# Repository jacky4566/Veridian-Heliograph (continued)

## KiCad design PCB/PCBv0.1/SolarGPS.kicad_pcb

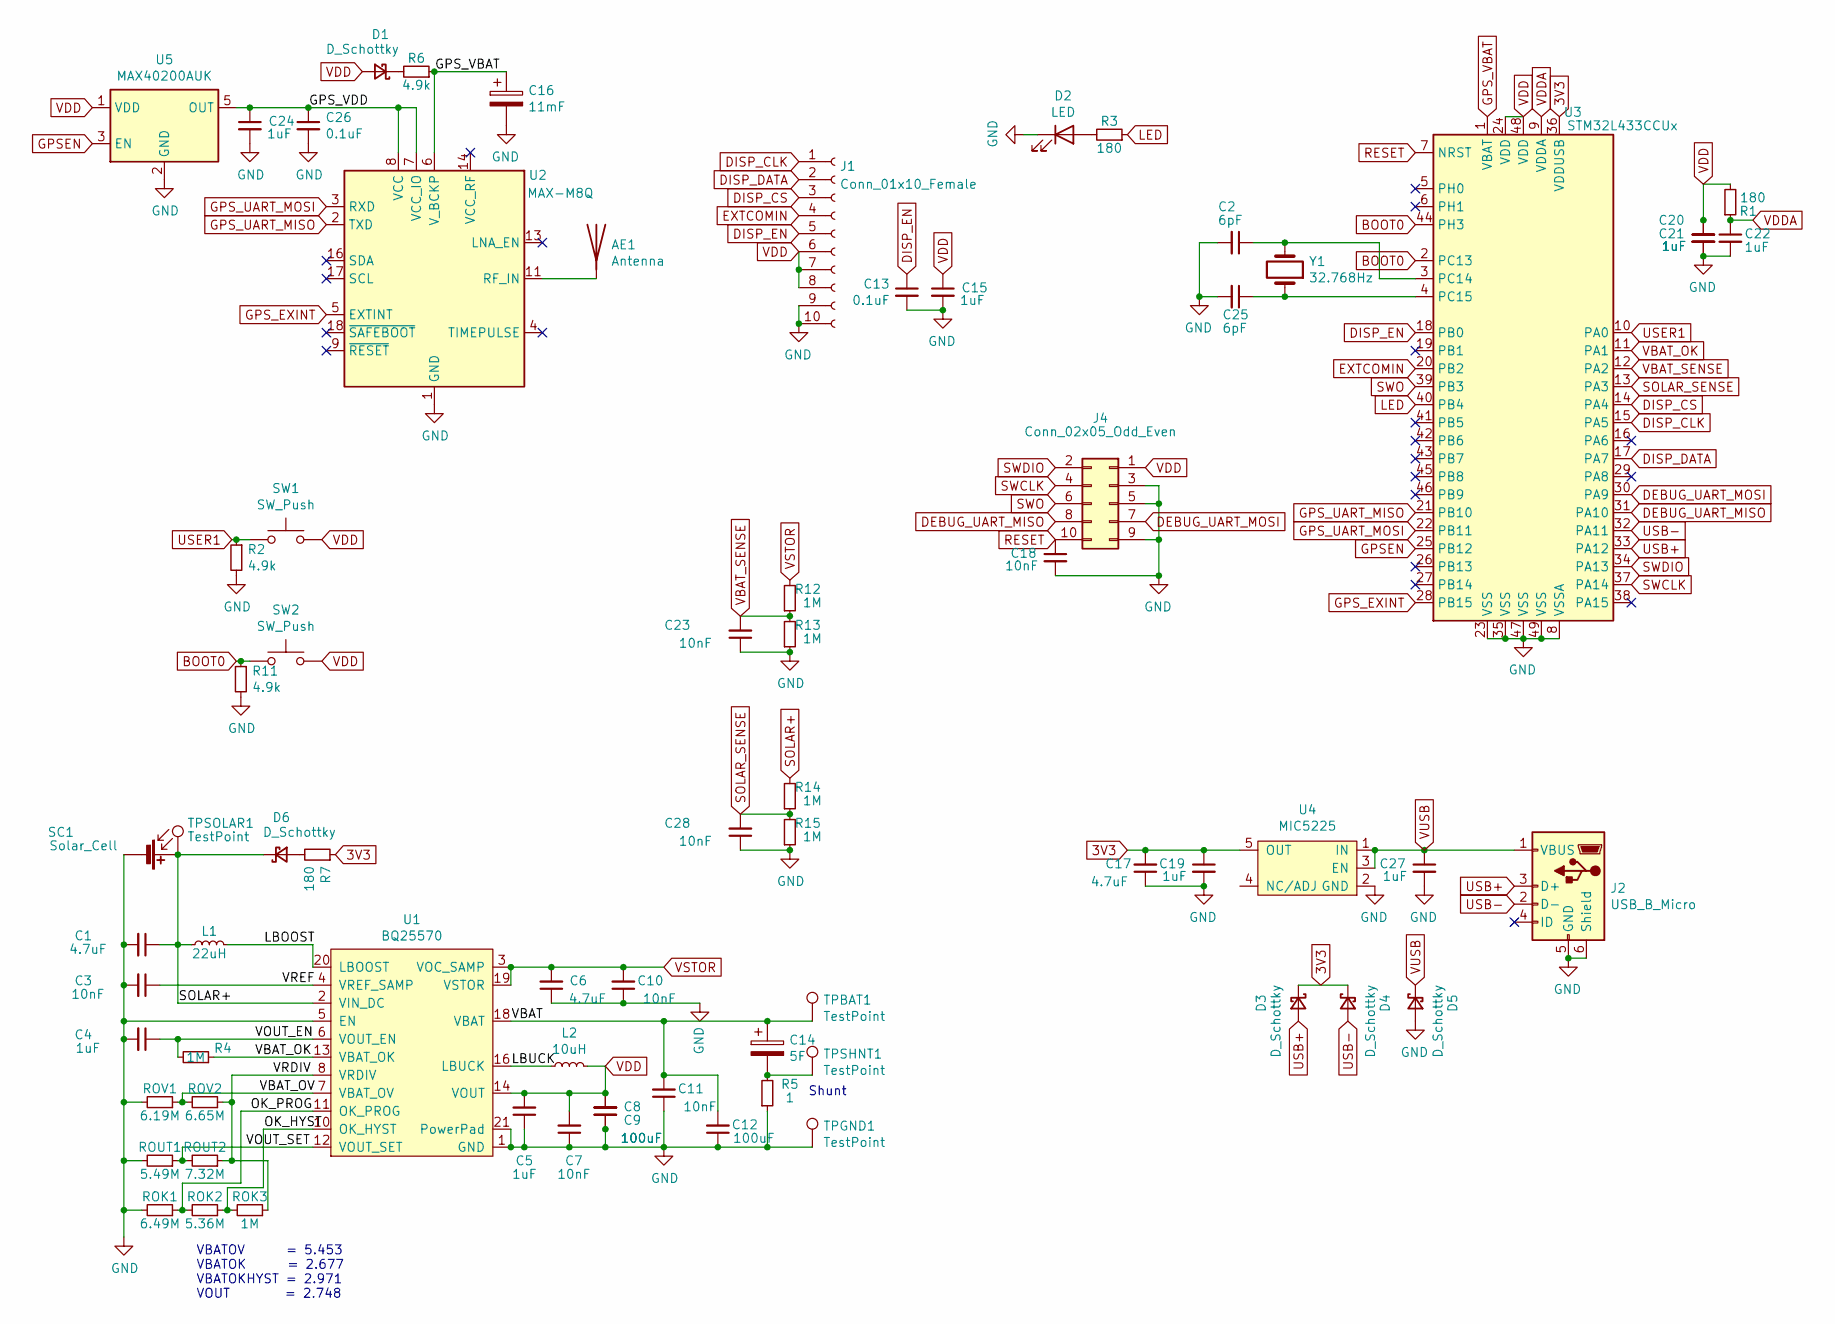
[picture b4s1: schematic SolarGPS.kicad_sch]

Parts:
AE1: Antenna; CGIP.25.4.A.02
C1, C6, C17: 4.7uF; C_0805_2012Metric
C2, C25: 6pF; C_0603_1608Metric
C3, C7, C10, C11, C18, C23, C28: 10nF; C_0603_1608Metric
C4, C5, C15, C19, C20, C21, C22, C24, C27: 1uF; C_0603_1608Metric
C8, C9, C12: 100uF; C_1206_3216Metric
C13, C26: 0.1uF; C_0603_1608Metric
C14: 5F; PinHeader_1x02_P2.54mm_Vertical
C16: 11mF; C_1210_3225Metric; Part CPH3225A
D1, D3, D4, D5, D6: D_Schottky; D_SOD-523
D2: LED; D_0805_2012Metric; PArt LTST-S270CKT
J1: Conn_01x10_Female; AYF531035
J2: USB_B_Micro; USB_Micro-B_GCT_USB3076-30-A
J4: Conn_02x05_Odd_Even; PinHeader_2x05_P2.00mm_Vertical_SMD
L1: 22uH; 744031220; Part 744031220
L2: 10uH; 744029100; Part 744029100
R1, R3, R7: 180; R_0603_1608Metric
R2, R6, R11: 4.9k; R_0603_1608Metric
R4, R12, R13, R14, R15: 1M; R_0603_1608Metric
R5: 1; R_0603_1608Metric
ROK1: 6.49M; R_0603_1608Metric
ROK2: 5.36M; R_0603_1608Metric
ROK3: 1M; R_0603_1608Metric
ROUT1: 5.49M; R_0603_1608Metric
ROUT2: 7.32M; R_0603_1608Metric
ROV1: 6.19M; R_0603_1608Metric
ROV2: 6.65M; R_0603_1608Metric
SC1: Solar_Cell; SM141K09L
SW1, SW2: SW_Push; SW_Push_1P1T_NO_6x6mm_H9.5mm; Part KSC471G 70SH LFS PF
TPBAT1: TestPoint; TestPoint_THTPad_1.0x1.0mm_Drill0.5mm
TPGND1: TestPoint; TestPoint_THTPad_1.0x1.0mm_Drill0.5mm
TPSHNT1: TestPoint; TestPoint_THTPad_1.0x1.0mm_Drill0.5mm
TPSOLAR1: TestPoint; TestPoint_THTPad_1.0x1.0mm_Drill0.5mm
U1: BQ25570; QFN-20-1EP_3.5x3.5mm_P0.5mm_EP2x2mm
U2: MAX-M8Q; ublox_MAX
U3: STM32L433CCUx; QFN-48-1EP_7x7mm_P0.5mm_EP5.6x5.6mm
U4: MIC5225; SOT-23-5
U5: MAX40200AUK; SOT-23-5
Y1: 32.768Hz; Crystal_SMD_3215-2Pin_3.2x1.5mm; Part CM315D

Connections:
3V3: C17.2, C19.1, D3.1 (K), D4.1 (K), R7.1, U3.36 (VDDUSB), U4.5 (OUT)
/GPS_VDD: C24.1, C26.1, U2.7 (VCC_IO), U2.8 (VCC), U5.5 (OUT)
/LBOOST: L1.2, U1.20 (LBOOST)
/LBUCK: L2.1, U1.16 (LBUCK)
/OK_HYST: ROK2.1, ROK3.2, U1.10 (OK_HYST)
/OK_PROG: ROK1.1, ROK2.2, U1.11 (OK_PROG)
/VBAT: C11.2, C12.2, C14.1, TPBAT1.1, U1.18 (VBAT)
/VBAT_OV: ROV1.1, ROV2.2, U1.7 (VBAT_OV)
/VOUT_EN: C4.1, R4.2, U1.6 (VOUT_EN)
/VOUT_SET: ROUT1.1, ROUT2.2, U1.12 (VOUT_SET)
/VRDIV: ROK3.1, ROUT2.1, ROV2.1, U1.8 (VRDIV)
/VREF: C3.1, U1.4 (VREF_SAMP)
BOOT0: R11.1, SW2.1, U3.2 (PC13), U3.44 (PH3)
DEBUG_UART_MISO: J4.8, U3.31 (PA10)
DEBUG_UART_MOSI: J4.7, U3.30 (PA9)
DISP_CLK: J1.1, U3.15 (PA5)
DISP_CS: J1.3, U3.14 (PA4)
DISP_DATA: J1.2, U3.17 (PA7)
DISP_EN: C13.1, J1.5, U3.18 (PB0)
EXTCOMIN: J1.4, U3.20 (PB2)
GND: C1.2, C2.2, C3.2, C4.2, C5.1, C6.1, C7.1, C8.1, C9.1, C10.1, C11.1, C12.1, C13.2, C15.2, C16.2, C17.1, C18.2, C19.2, C20.2, C21.2, C22.2, C23.1, C24.2, C25.2, C26.2, C27.2, C28.1, D2.1 (K), D5.2 (A), J1.9, J1.10, J2.5 (GND), J2.6 (Shield), J4.3, J4.5, J4.9, R2.2, R5.1, R11.2, R13.1, R15.1, ROK1.2, ROUT1.2, ROV1.2, SC1.2 (-), TPGND1.1, U1.1 (GND), U1.5 (EN), U1.9 (GND), U1.15 (GND), U1.17 (GND), U1.21 (PowerPad), U2.1 (GND), U2.10 (GND), U2.12 (GND), U3.8 (VSSA), U3.23 (VSS), U3.35 (VSS), U3.47 (VSS), U3.49 (VSS), U4.2 (GND), U5.2 (GND)
GPSEN: U3.25 (PB12), U5.3 (EN)
GPS_EXINT: U2.5 (EXTINT), U3.28 (PB15)
GPS_UART_MISO: U2.2 (TXD), U3.21 (PB10)
GPS_UART_MOSI: U2.3 (RXD), U3.22 (PB11)
GPS_VBAT: C16.1, R6.1, U2.6 (V_BCKP), U3.1 (VBAT)
LED: R3.1, U3.40 (PB4)
unnamed: AE1.1 (A), U2.11 (RF_IN)
unnamed: C2.1, U3.3 (PC14), Y1.2
unnamed: C14.2, R5.2, TPSHNT1.1
unnamed: C25.1, U3.4 (PC15), Y1.1
unnamed: D1.1 (K), R6.2
unnamed: D2.2 (A), R3.2
unnamed: D6.2 (A), R7.2
RESET: C18.1, J4.10, U3.7 (NRST)
SOLAR+: C1.1, D6.1 (K), L1.1, R14.2, SC1.1 (+), TPSOLAR1.1, U1.2 (VIN_DC)
SOLAR_SENSE: C28.2, R14.1, R15.2, U3.13 (PA3)
SWCLK: J4.4, U3.37 (PA14)
SWDIO: J4.2, U3.34 (PA13)
SWO: J4.6, U3.39 (PB3)
USB+: D3.2 (A), J2.3 (D+), U3.33 (PA12)
USB-: D4.2 (A), J2.2 (D-), U3.32 (PA11)
USER1: R2.1, SW1.1, U3.10 (PA0)
VBAT_OK: R4.1, U1.13 (VBAT_OK), U3.11 (PA1)
VBAT_SENSE: C23.2, R12.1, R13.2, U3.12 (PA2)
VDD: C5.2, C7.2, C8.2, C9.2, C15.1, C20.1, C21.1, D1.2 (A), J1.6, J1.7, J1.8, J4.1, L2.2, R1.2, SW1.2, SW2.2, U1.14 (VOUT), U3.24 (VDD), U3.48 (VDD), U5.1 (VDD)
VDDA: C22.1, R1.1, U3.9 (VDDA)
VSTOR: C6.2, C10.2, R12.2, U1.3 (VOC_SAMP), U1.19 (VSTOR)
VUSB: C27.1, D5.1 (K), J2.1 (VBUS), U4.1 (IN), U4.3 (EN)

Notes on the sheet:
VBATOV = 5.453 VBATOK = 2.677 VBATOKHYST = 2.971 VOUT = 2.748
Shunt

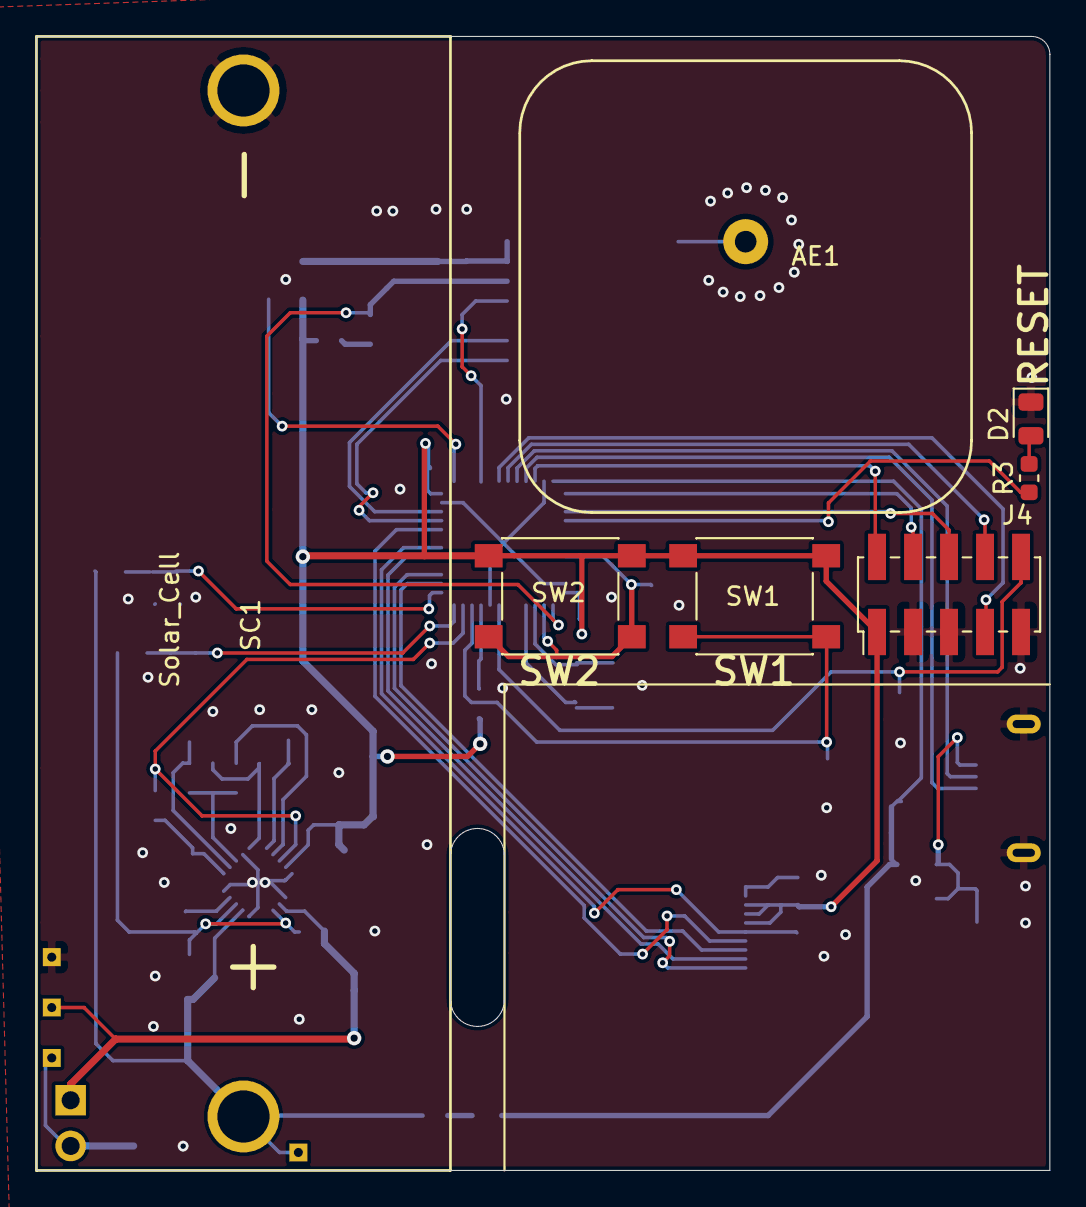
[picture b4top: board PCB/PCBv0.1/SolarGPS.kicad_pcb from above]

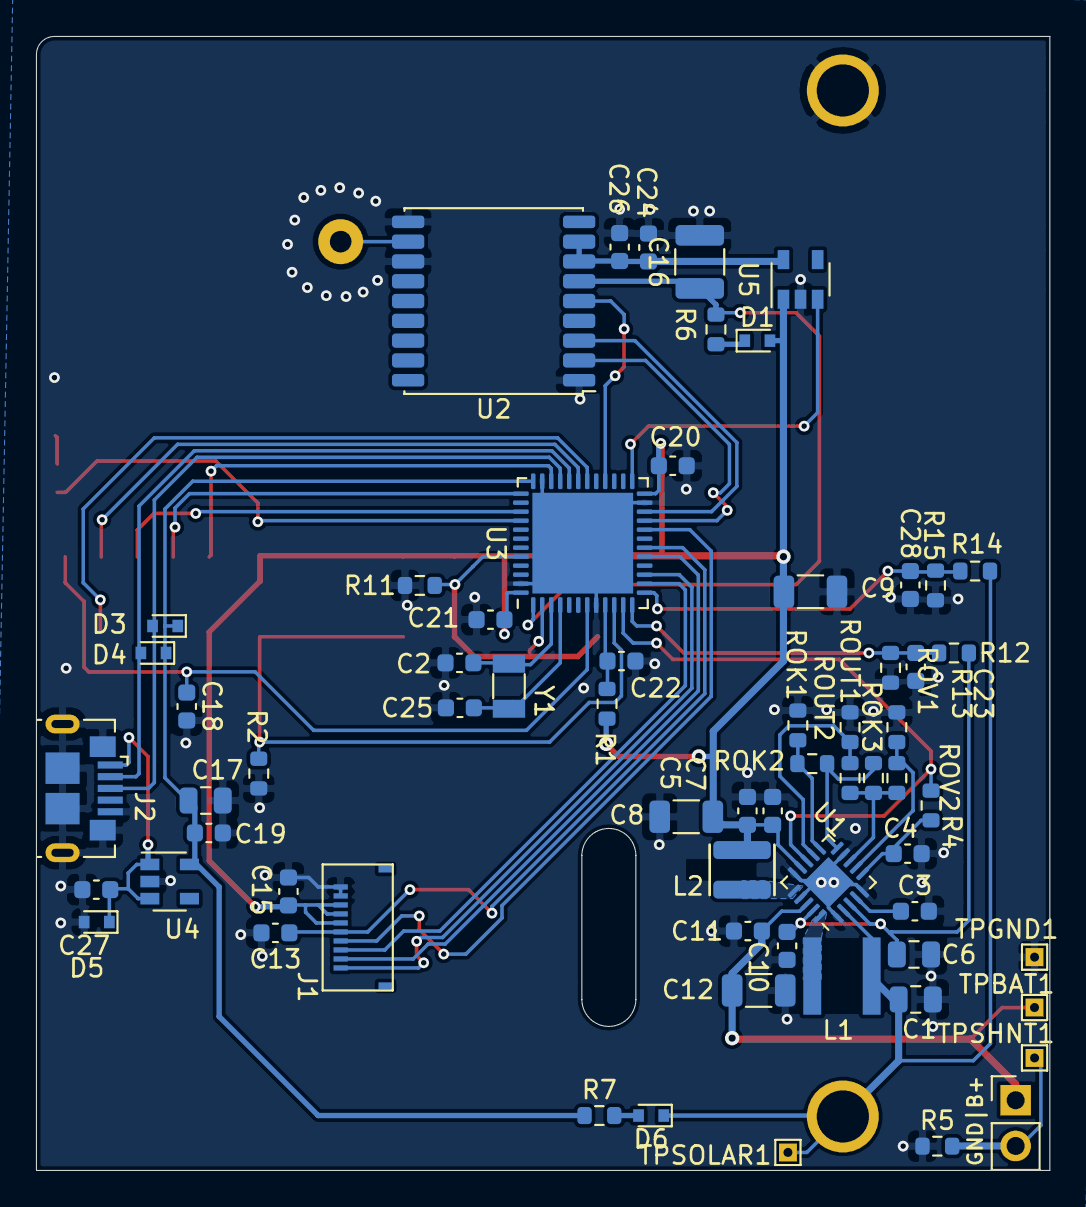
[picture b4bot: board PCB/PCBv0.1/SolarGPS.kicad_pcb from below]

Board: 2 copper layers, 56.3 x 63.0 mm, 72 parts (65 on the bottom side), 49 nets.

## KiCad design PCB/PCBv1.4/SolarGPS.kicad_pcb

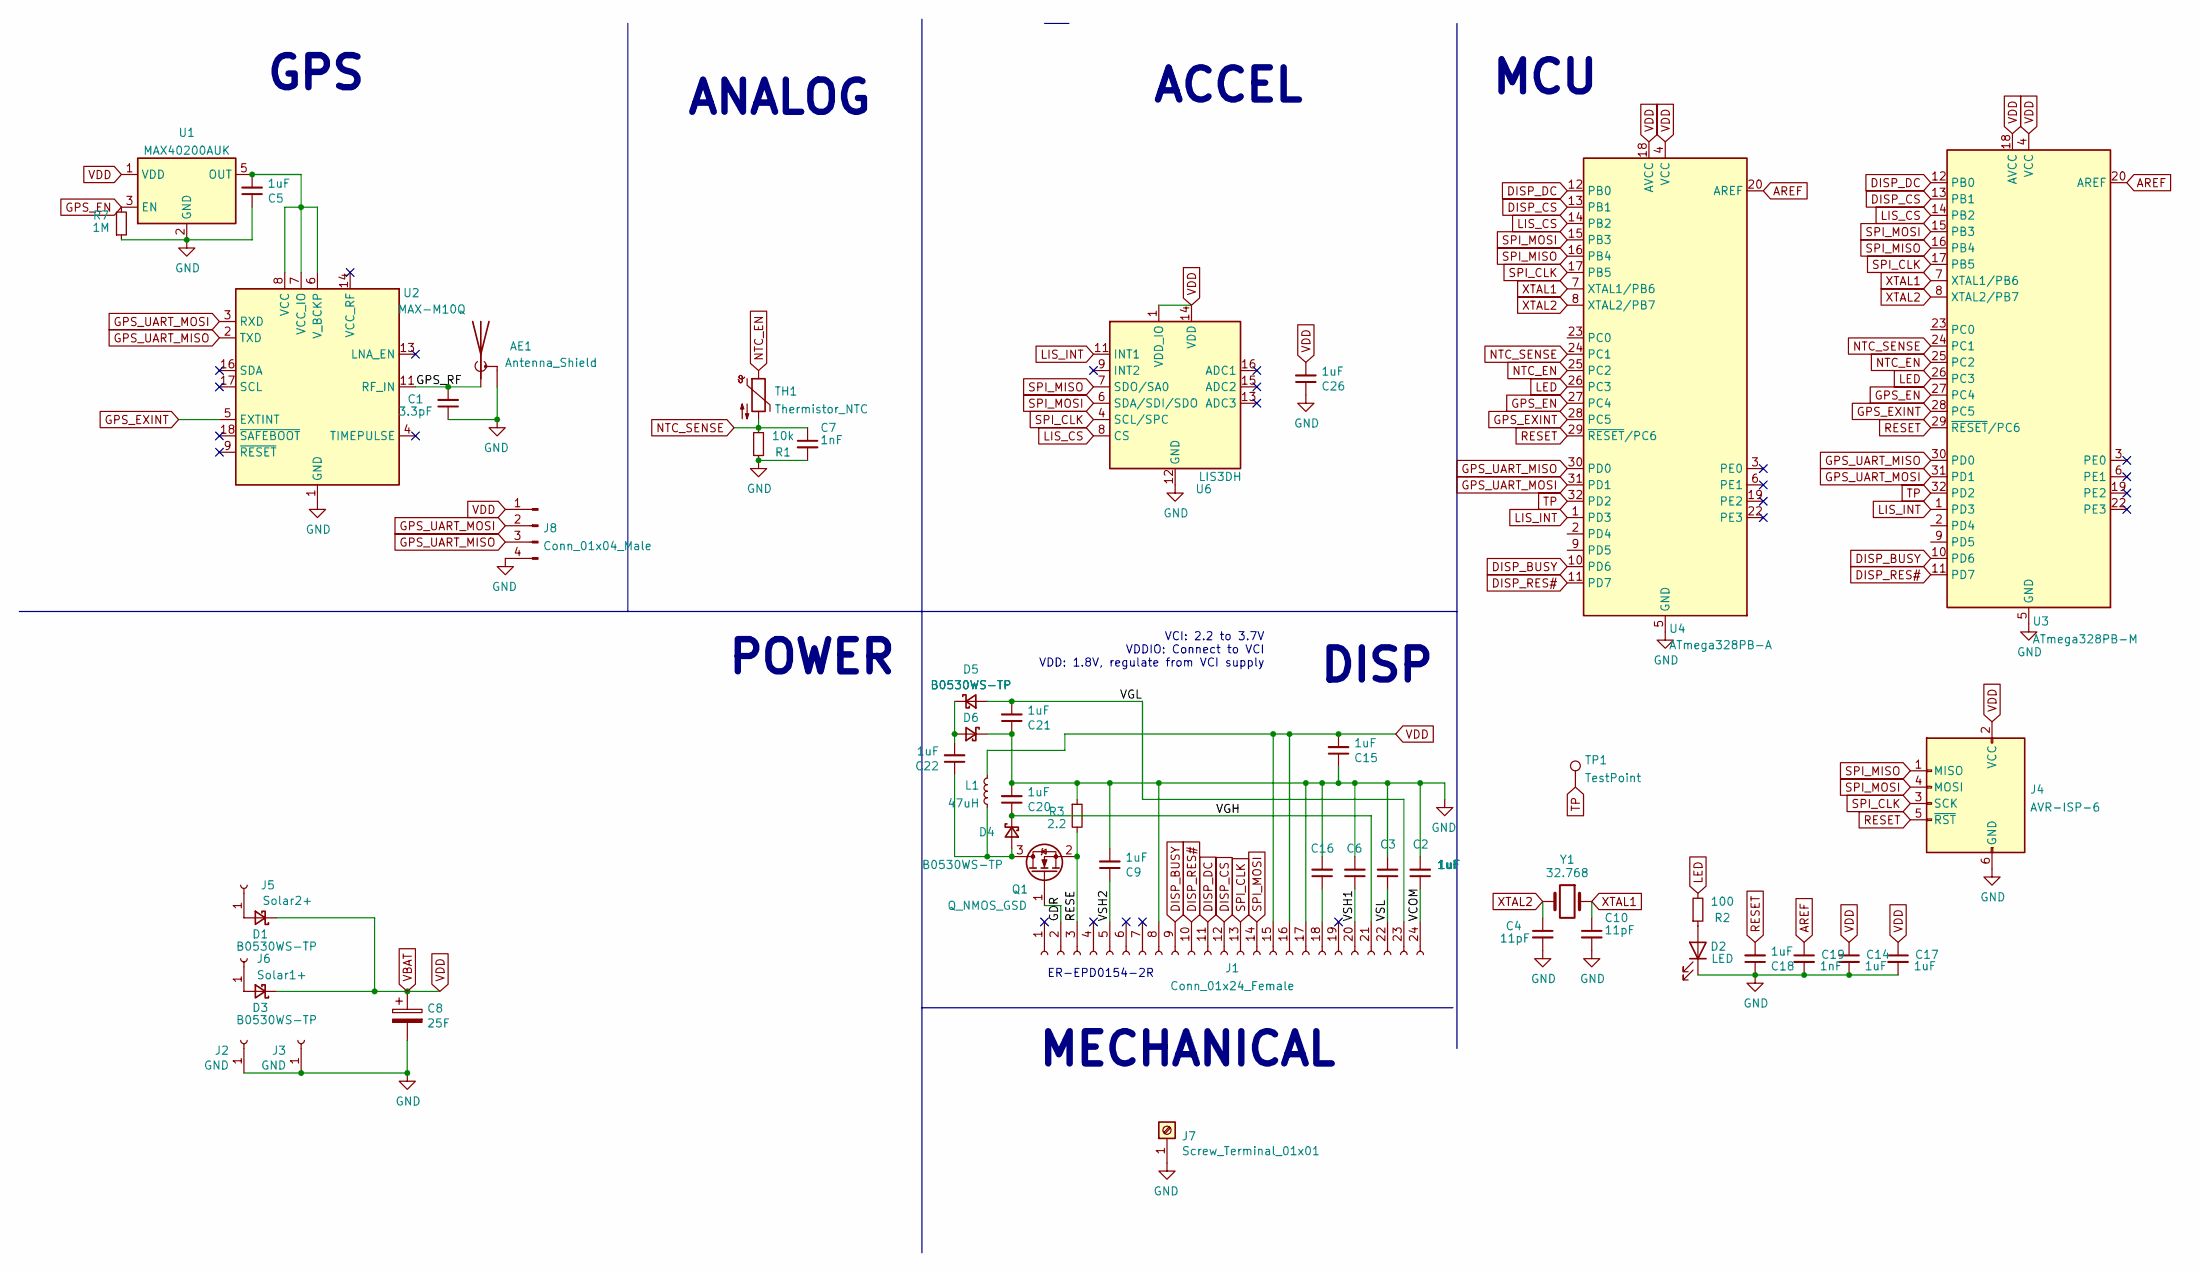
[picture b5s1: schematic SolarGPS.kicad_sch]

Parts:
AE1: Antenna_Shield; Pulse_W3011; Part W3011A
C1: 3.3pF; C_0402_1005Metric
C2, C3, C5, C6, C9, C14, C15, C16, C17, C18, C20, C21, C22, C26: 1uF; C_0603_1608Metric
C4, C10: 11pF; C_0603_1608Metric
C7, C19: 1nF; C_0603_1608Metric
C8: 25F; TPLC3R8-25MR8X20; Part TPLC3R8-25MR8X20
D1, D3: B0530WS-TP; D_SOD-323; Part B0530WS
D2: LED; D_0805_2012Metric; Part LTST-S220KRKT
D4, D5, D6: B0530WS-TP; D_SOD-323
J1: Conn_01x24_Female; ER-CON24HT-1
J2, J3: GND; PinHeader_1x01_P2.54mm_Vertical
J4: AVR-ISP-6; PinHeader_2x03_P2.54mm_Vertical
J5: Solar2+; PinHeader_1x01_P2.54mm_Vertical
J6: Solar1+; PinHeader_1x01_P2.54mm_Vertical
J7: Screw_Terminal_01x01; M4_RA_7792; Part 7792
J8: Conn_01x04_Male; PinSocket_1x04_P2.54mm_Vertical
L1: 47uH; L_Taiyo-Yuden_NR-40xx; Part NR4018T470M
Q1: Q_NMOS_GSD; SOT-23; Part DMN3730U-7
R1: 10k; R_0603_1608Metric
R2: 100; R_0603_1608Metric
R3: 2.2; R_0603_1608Metric
R7: 1M; R_0603_1608Metric
TH1: Thermistor_NTC; R_0603_1608Metric; Part NTCG163JF103FT1
TP1: TestPoint; TestPoint_Loop_D2.50mm_Drill1.0mm_LowProfile
U1: MAX40200AUK; SOT-23-5
U2: MAX-M10Q; ublox_MAX
U3: ATmega328PB-M; QFN-32-1EP_5x5mm_P0.5mm_EP3.1x3.1mm
U4: ATmega328PB-A; TQFP-32_7x7mm_P0.8mm
U6: LIS3DH; LGA-16_3x3mm_P0.5mm_LayoutBorder3x5y
Y1: 32.768; Crystal_SMD_3215-2Pin_3.2x1.5mm; Part SC32S-7PF20PPM

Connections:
/GDR: J1.2, Q1.1 (G)
/GPS_RF: AE1.1 (A), C1.2, U2.11 (RF_IN)
/RESE: J1.3, Q1.2 (S), R3.2
/VCOM: C2.1, J1.24
/VGH: C20.1, D4.1 (K), J1.21
/VGL: C21.2, D5.2 (A), J1.23
/VSH1: C6.1, J1.20
/VSH2: C9.1, J1.5
/VSL: C3.1, J1.22
AREF: C19.1, U3.20 (AREF), U4.20 (AREF)
DISP_BUSY: J1.9, U3.10 (PD6), U4.10 (PD6)
DISP_CS: J1.12, U3.13 (PB1), U4.13 (PB1)
DISP_DC: J1.11, U3.12 (PB0), U4.12 (PB0)
DISP_RES#: J1.10, U3.11 (PD7), U4.11 (PD7)
GND: AE1.2 (Shield), C1.1, C2.2, C3.2, C4.2, C5.1, C6.2, C7.2, C8.2, C9.2, C10.2, C14.2, C15.1, C16.2, C17.2, C18.1, C19.2, C20.2, C21.1, C26.1, D2.1 (K), D6.1 (K), J1.8, J1.17, J2.1, J3.1, J4.6 (GND), J7.1, J8.4, R1.1, R3.1, R7.1, U1.2 (GND), U2.1 (GND), U2.10 (GND), U2.12 (GND), U3.5 (GND), U3.21 (GND), U3.33 (GND), U4.5 (GND), U4.21 (GND), U6.5 (GND), U6.10 (GND), U6.12 (GND)
GPS_EN: R7.2, U1.3 (EN), U3.27 (PC4), U4.27 (PC4)
GPS_EXINT: U2.5 (EXTINT), U3.28 (PC5), U4.28 (PC5)
GPS_UART_MISO: J8.3, U2.2 (TXD), U3.30 (PD0), U4.30 (PD0)
GPS_UART_MOSI: J8.2, U2.3 (RXD), U3.31 (PD1), U4.31 (PD1)
LED: R2.2, U3.26 (PC3), U4.26 (PC3)
LIS_CS: U3.14 (PB2), U4.14 (PB2), U6.8 (CS)
LIS_INT: U3.1 (PD3), U4.1 (PD3), U6.11 (INT1)
NTC_EN: TH1.1, U3.25 (PC2), U4.25 (PC2)
NTC_SENSE: C7.1, R1.2, TH1.2, U3.24 (PC1), U4.24 (PC1)
unnamed: C5.2, U1.5 (OUT), U2.6 (V_BCKP), U2.7 (VCC_IO), U2.8 (VCC)
unnamed: C16.1, J1.18
unnamed: C22.1, D4.2 (A), L1.2, Q1.3 (D)
unnamed: C22.2, D5.1 (K), D6.2 (A)
unnamed: D1.2 (A), J5.1
unnamed: D2.2 (A), R2.1
unnamed: D3.2 (A), J6.1
RESET: C18.2, J4.5 (~RST), U3.29 (~RESET/PC6), U4.29 (~RESET/PC6)
SPI_CLK: J1.13, J4.3 (SCK), U3.17 (PB5), U4.17 (PB5), U6.4 (SCL/SPC)
SPI_MISO: J4.1 (MISO), U3.16 (PB4), U4.16 (PB4), U6.7 (SDO/SA0)
SPI_MOSI: J1.14, J4.4 (MOSI), U3.15 (PB3), U4.15 (PB3), U6.6 (SDA/SDI/SDO)
TP: TP1.1, U3.32 (PD2), U4.32 (PD2)
VBAT: C8.1, C14.1, C15.2, C17.1, C26.2, D1.1 (K), D3.1 (K), J1.15, J1.16, J4.2 (VCC), J8.1, L1.1, U1.1 (VDD), U3.4 (VCC), U3.18 (AVCC), U4.4 (VCC), U4.18 (AVCC), U6.1 (VDD_IO), U6.14 (VDD)
XTAL1: C10.1, U3.7 (XTAL1/PB6), U4.7 (XTAL1/PB6), Y1.1
XTAL2: C4.1, U3.8 (XTAL2/PB7), U4.8 (XTAL2/PB7), Y1.2

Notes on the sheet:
GPS
MCU
ACCEL
ER-EPD0154-2R
DISP
POWER
MECHANICAL
VCI: 2.2 to 3.7V VDDIO: Connect to VCI VDD: 1.8V, regulate from VCI supply
ANALOG

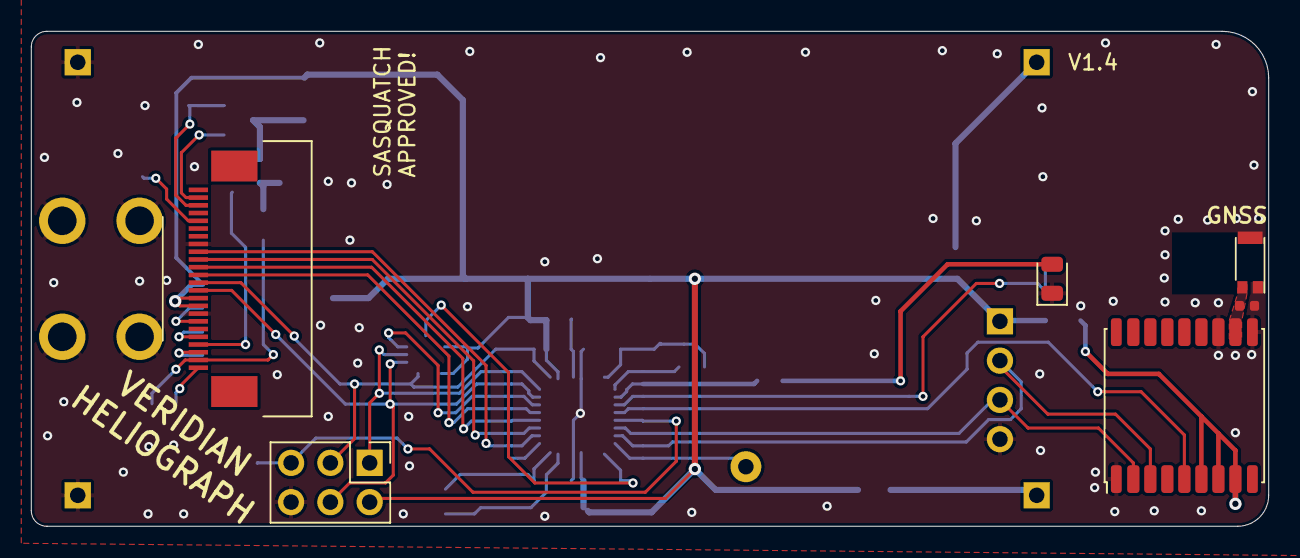
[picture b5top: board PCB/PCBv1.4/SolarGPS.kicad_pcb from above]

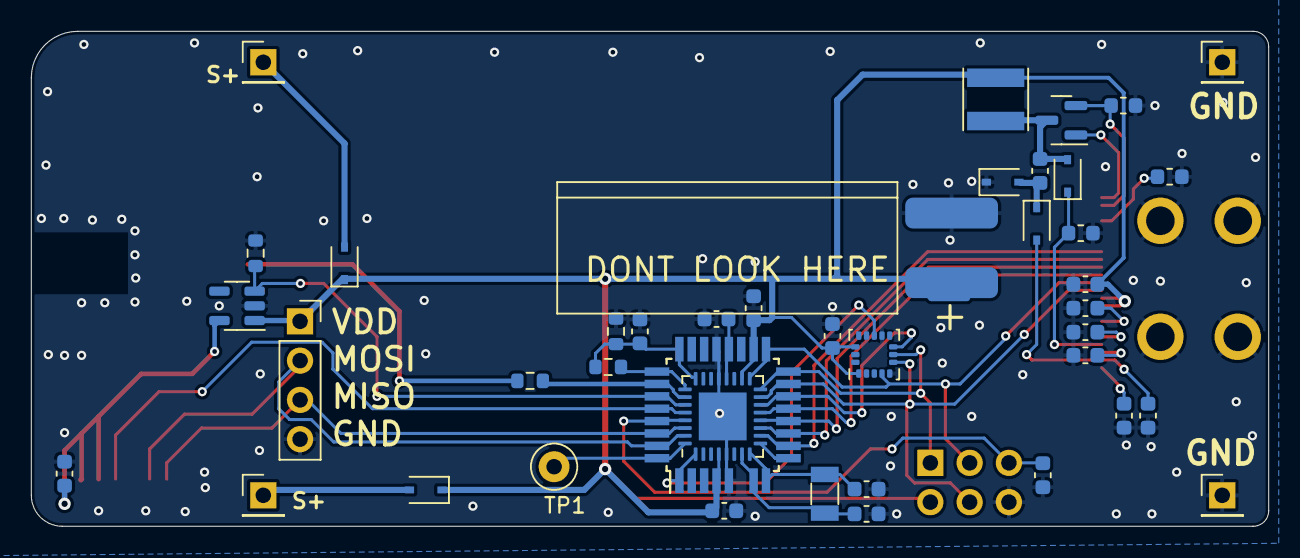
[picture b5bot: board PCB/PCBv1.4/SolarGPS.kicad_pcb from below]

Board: 2 copper layers, 80.0 x 32.0 mm, 49 parts (42 on the bottom side), 39 nets.

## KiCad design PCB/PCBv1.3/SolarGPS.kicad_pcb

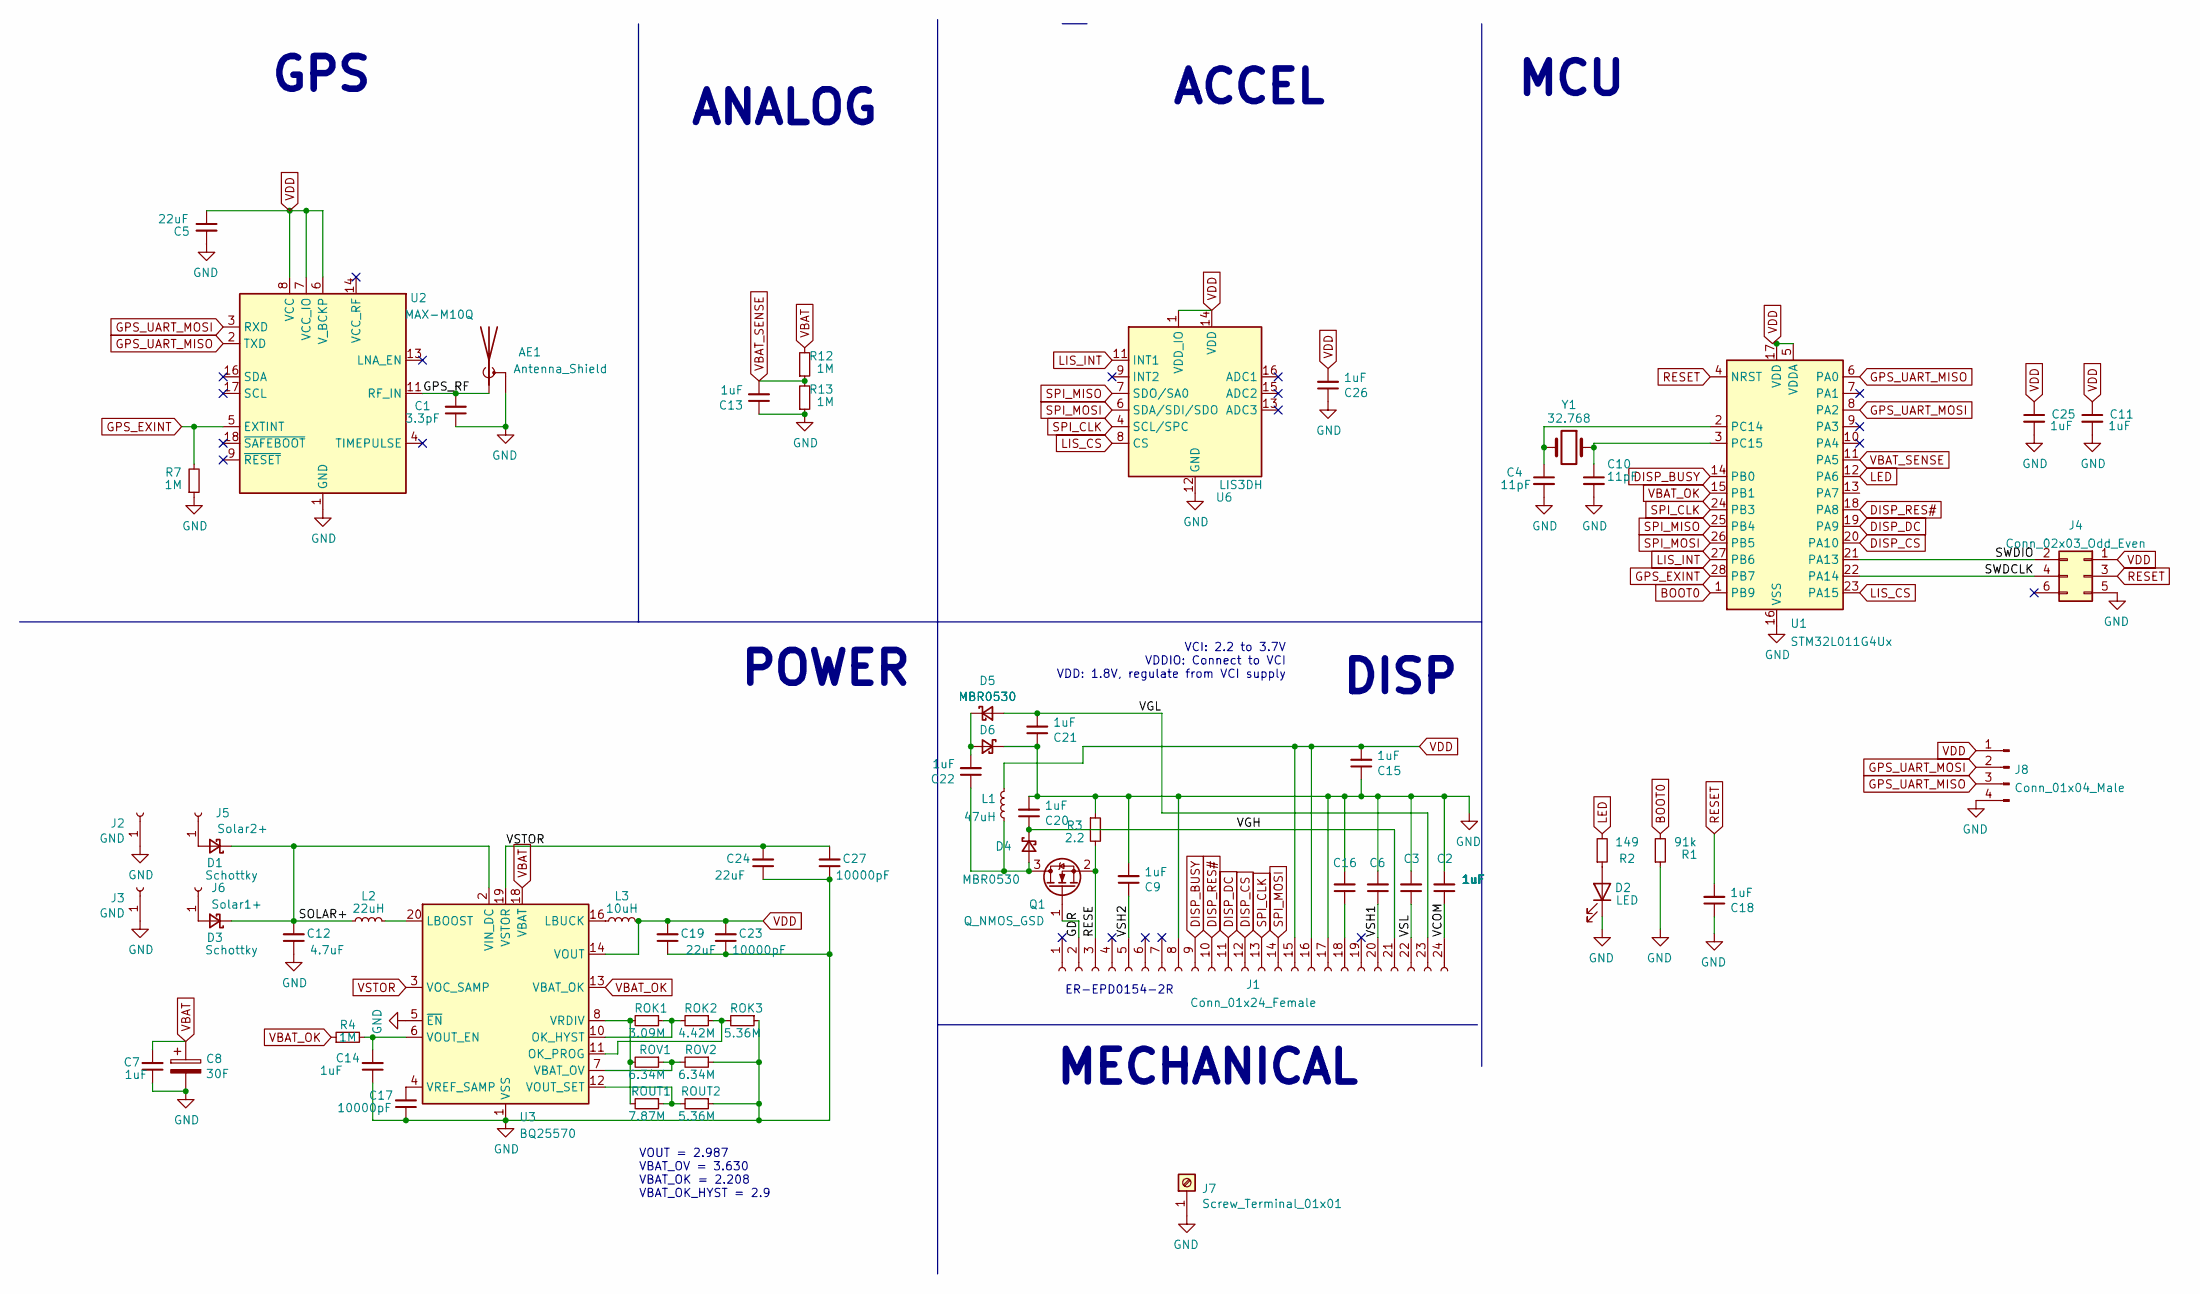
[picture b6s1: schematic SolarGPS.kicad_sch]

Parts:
AE1: Antenna_Shield; Pulse_W3011; Part W3011A
C1: 3.3pF; C_0402_1005Metric
C2, C3, C6, C7, C9, C11, C13, C14, C15, C16, C18, C20, C21, C22, C25, C26: 1uF; C_0603_1608Metric
C4, C10: 11pF; C_0603_1608Metric
C5: 22uF; C_0603_1608Metric; Part GRM187R61A226ME15
C8: 30F; SCCT30E156SRB
C12: 4.7uF; C_0805_2012Metric
C17, C23, C27: 10000pF; C_0603_1608Metric
C19, C24: 22uF; C_0805_2012Metric
D1, D3: Schottky; D_SOD-323_HandSoldering; Part B0530WS
D2: LED; D_0805_2012Metric; Part LS R976-NR-1
D4, D5, D6: MBR0530; D_SOD-123
J1: Conn_01x24_Female; ER-CON24HT-1
J2, J3: GND; PinHeader_1x01_P2.54mm_Vertical
J4: Conn_02x03_Odd_Even; Tag-Connect_TC2030-IDC-NL_2x03_P1.27mm_Vertical
J5: Solar2+; PinHeader_1x01_P2.54mm_Vertical
J6: Solar1+; PinHeader_1x01_P2.54mm_Vertical
J7: Screw_Terminal_01x01; M4_RA_7792; Part 7792
J8: Conn_01x04_Male; PinSocket_1x04_P2.54mm_Vertical
L1: 47uH; L_Taiyo-Yuden_NR-40xx; Part NR4018T470M
L2: 22uH; 744031220; Part 744031220
L3: 10uH; 744029100; Part 744029100
Q1: Q_NMOS_GSD; SOT-23; Part NX3008NBK
R1: 91k; R_0603_1608Metric
R2: 149; R_0603_1608Metric
R3: 2.2; R_0603_1608Metric
R4, R7, R12, R13: 1M; R_0603_1608Metric
ROK1: 3.09M; R_0603_1608Metric
ROK2: 4.42M; R_0603_1608Metric
ROK3: 5.36M; R_0603_1608Metric
ROUT1: 7.87M; R_0603_1608Metric
ROUT2: 5.36M; R_0603_1608Metric
ROV1, ROV2: 6.34M; R_0603_1608Metric
U1: STM32L011G4Ux; QFN-28_4x4mm_P0.5mm
U2: MAX-M10Q; ublox_MAX
U3: BQ25570; QFN-20-1EP_3.5x3.5mm_P0.5mm_EP2x2mm
U6: LIS3DH; LGA-16_3x3mm_P0.5mm_LayoutBorder3x5y
Y1: 32.768; Crystal_SMD_3215-2Pin_3.2x1.5mm; Part SC32S-7PF20PPM

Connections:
/GDR: J1.2, Q1.1 (G)
/GPS_RF: AE1.1 (A), C1.2, U2.11 (RF_IN)
/RESE: J1.3, Q1.2 (S), R3.2
/SOLAR+: C12.2, D1.1 (K), D3.1 (K), L2.1, U3.2 (VIN_DC)
/SWDCLK: J4.4, U1.22 (PA14)
/SWDIO: J4.2, U1.21 (PA13)
/VCOM: C2.1, J1.24
/VGH: C20.1, D4.1 (K), J1.21
/VGL: C21.2, D5.2 (A), J1.23
/VSH1: C6.1, J1.20
/VSH2: C9.1, J1.5
/VSL: C3.1, J1.22
BOOT0: R1.2, U1.1 (PB9)
DISP_BUSY: J1.9, U1.14 (PB0)
DISP_CS: J1.12, U1.20 (PA10)
DISP_DC: J1.11, U1.19 (PA9)
DISP_RES#: J1.10, U1.18 (PA8)
GND: AE1.2 (Shield), C1.1, C2.2, C3.2, C4.2, C5.2, C6.2, C7.1, C8.2, C9.2, C10.2, C11.2, C12.1, C13.1, C14.1, C15.1, C16.2, C17.1, C18.1, C19.1, C20.2, C21.1, C23.1, C24.1, C25.2, C26.1, C27.1, D2.1 (K), D6.1 (K), J1.8, J1.17, J2.1, J3.1, J4.5, J7.1, J8.4, R1.1, R3.1, R7.1, R13.1, ROK3.1, ROUT2.1, ROV2.1, U1.16 (VSS), U2.1 (GND), U2.10 (GND), U2.12 (GND), U3.1 (VSS), U3.5 (~EN), U3.9 (VSS), U3.15 (VSS), U3.17 (VSS), U3.21 (VSS), U6.5 (GND), U6.10 (GND), U6.12 (GND)
GPS_EXINT: R7.2, U1.28 (PB7), U2.5 (EXTINT)
GPS_UART_MISO: J8.3, U1.6 (PA0), U2.2 (TXD)
GPS_UART_MOSI: J8.2, U1.8 (PA2), U2.3 (RXD)
LED: R2.2, U1.12 (PA6)
LIS_CS: U1.23 (PA15), U6.8 (CS)
LIS_INT: U1.27 (PB6), U6.11 (INT1)
unnamed: C4.1, U1.2 (PC14), Y1.2
unnamed: C10.1, U1.3 (PC15), Y1.1
unnamed: C14.2, R4.2, U3.6 (VOUT_EN)
unnamed: C16.1, J1.18
unnamed: C17.2, U3.4 (VREF_SAMP)
unnamed: C22.1, D4.2 (A), L1.2, Q1.3 (D)
unnamed: C22.2, D5.1 (K), D6.2 (A)
unnamed: D1.2 (A), J5.1
unnamed: D2.2 (A), R2.1
unnamed: D3.2 (A), J6.1
unnamed: L2.2, U3.20 (LBOOST)
unnamed: L3.1, U3.16 (LBUCK)
unnamed: ROK1.1, ROK2.2, U3.10 (OK_HYST)
unnamed: ROK1.2, ROUT1.2, ROV1.2, U3.8 (VRDIV)
unnamed: ROK2.1, ROK3.2, U3.11 (OK_PROG)
unnamed: ROUT1.1, ROUT2.2, U3.12 (VOUT_SET)
unnamed: ROV1.1, ROV2.2, U3.7 (VBAT_OV)
RESET: C18.2, J4.3, U1.4 (NRST)
SPI_CLK: J1.13, U1.24 (PB3), U6.4 (SCL/SPC)
SPI_MISO: U1.25 (PB4), U6.7 (SDO/SA0)
SPI_MOSI: J1.14, U1.26 (PB5), U6.6 (SDA/SDI/SDO)
VBAT: C7.2, C8.1, R12.2, U3.18 (VBAT)
VBAT_OK: R4.1, U1.15 (PB1), U3.13 (VBAT_OK)
VBAT_SENSE: C13.2, R12.1, R13.2, U1.11 (PA5)
VDD: C5.1, C11.1, C15.2, C19.2, C23.2, C25.1, C26.2, J1.15, J1.16, J4.1, J8.1, L1.1, L3.2, U1.5 (VDDA), U1.17 (VDD), U2.6 (V_BCKP), U2.7 (VCC_IO), U2.8 (VCC), U3.14 (VOUT), U6.1 (VDD_IO), U6.14 (VDD)
VSTOR: C24.2, C27.2, U3.3 (VOC_SAMP), U3.19 (VSTOR)

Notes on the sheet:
GPS
MCU
ACCEL
ER-EPD0154-2R
DISP
VOUT = 2.987 VBAT_OV = 3.630 VBAT_OK = 2.208 VBAT_OK_HYST = 2.9
POWER
ANALOG
MECHANICAL
VCI: 2.2 to 3.7V VDDIO: Connect to VCI VDD: 1.8V, regulate from VCI supply

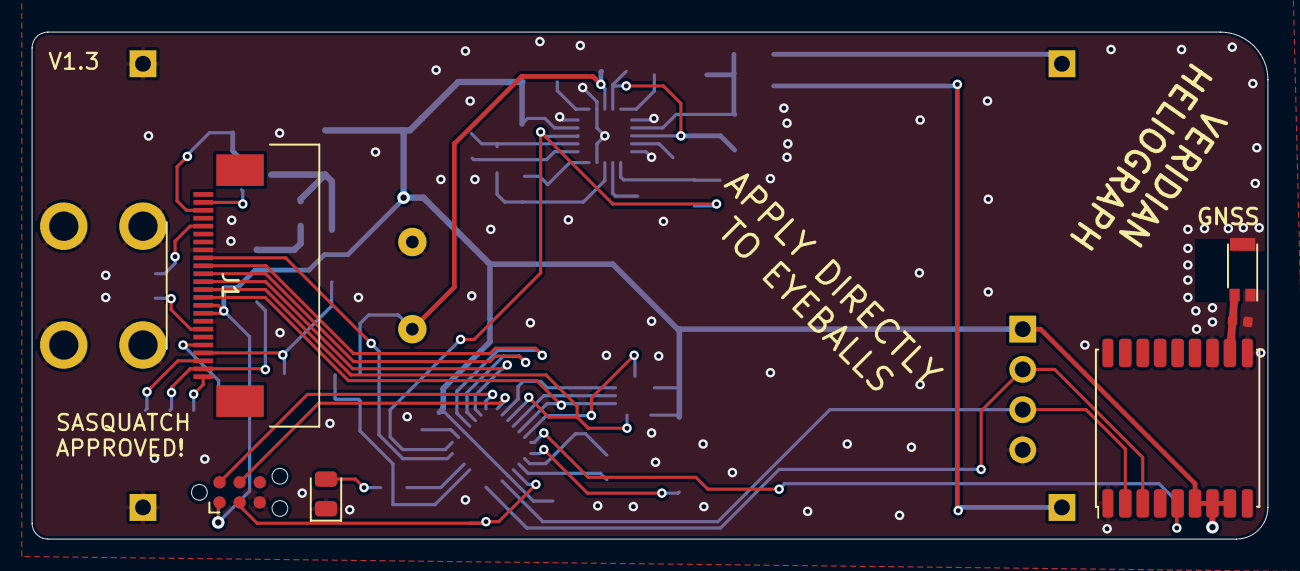
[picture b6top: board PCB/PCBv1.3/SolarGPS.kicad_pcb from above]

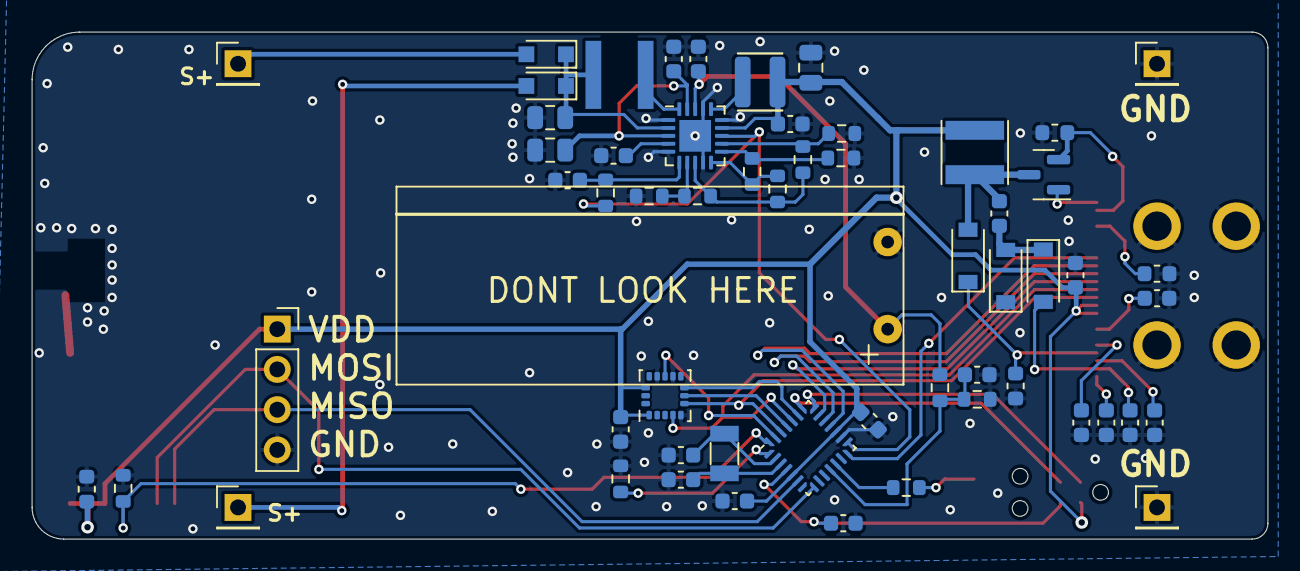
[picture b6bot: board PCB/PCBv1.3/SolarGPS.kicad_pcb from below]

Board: 2 copper layers, 78.0 x 32.0 mm, 65 parts (58 on the bottom side), 50 nets.
